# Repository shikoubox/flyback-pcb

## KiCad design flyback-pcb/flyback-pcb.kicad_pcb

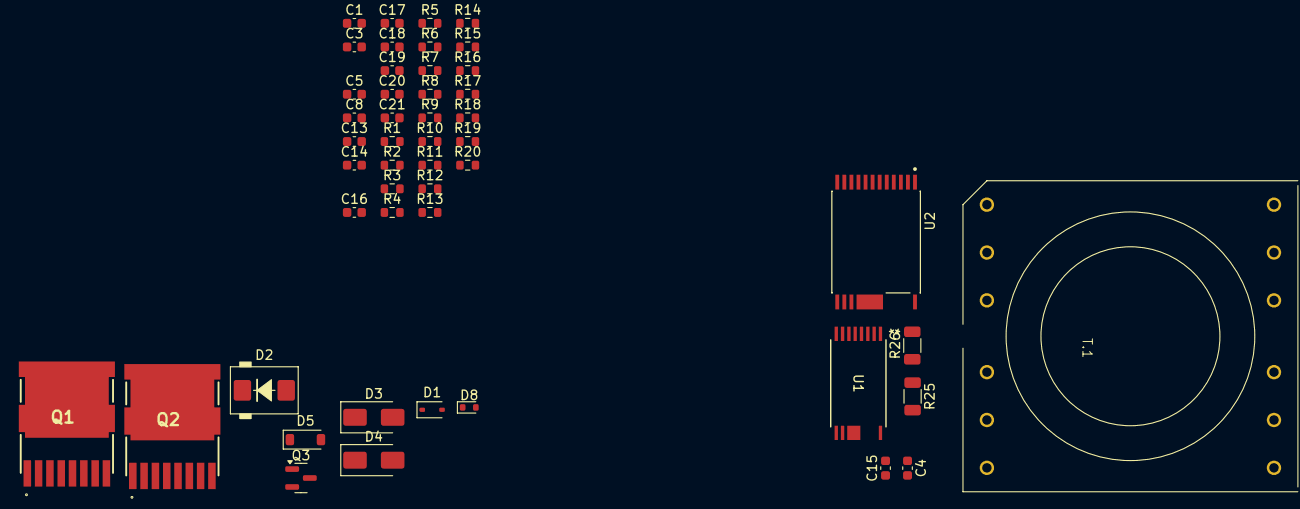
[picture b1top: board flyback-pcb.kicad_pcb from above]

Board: 2 copper layers, 48 parts (0 on the bottom side), 35 nets.

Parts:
C1: 470pF; C_0603_1608Metric
C3, C15, C16, C18, C19: 2.2nF; C_0603_1608Metric
C4: 39uF; C_0603_1608Metric
C5: 100uF; C_0603_1608Metric
C8: 1nF; C_0603_1608Metric
C13, C14: 330uF; C_0603_1608Metric
C17: 22uF; C_0603_1608Metric
C20, C21: 4.7uF; C_0603_1608Metric
D1: BAV19WS; D_SOD-323
D2: S3MB-13-F; D_SMBFL
D3, D4: S1G-E3/61T; D_SMA
D5: MMSZ5263; D_SOD-123
D8: BZT585-B10T; D_SOD-523
Q1, Q2: H-PSOF8L-11.68X9.80_1
Q3: MMBTA06; SOT-23
R1, R5, R7, R8: 20R; R_0603_1608Metric
R2: 2M; R_0603_1608Metric
R3, R4: 680K; R_0603_1608Metric
R6: 1.8M; R_0603_1608Metric
R9: 100R; R_0603_1608Metric
R10: 100K; R_0603_1608Metric
R11, R12: 47R; R_0603_1608Metric
R13: NCU18WF104F60RB; R_0603_1608Metric
R14: 0R; R_0603_1608Metric
R15: 3.65K; R_0603_1608Metric
R16: 11.8K; R_0603_1608Metric
R17, R18: 22R; R_0603_1608Metric
R19: 10R; R_0603_1608Metric
R20: 9mR; R_0603_1608Metric
R25: ERJ-8GEYJ395V; R_1206_3216Metric
R26: ERJ-8GEYJ105V; R_1206_3216Metric
T.1: B65879A
U1: MIN1072M-TL; MINSOP-16A_PWI
U2: INN3865CH801TL; IC_INN3865CH801TL

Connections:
GND: C13.2, C14.2, C16.1, C18.1, C19.1, C21.2, Q1.2 (S), Q1.3 (S), Q1.4 (S), Q1.5 (S), Q1.6 (S), Q1.7 (S), Q1.8 (S), R13.2 (-), R20.2, U2.2
HV_DC+: C1.2, C3.1, C4.1, C5.1, C15.2, R2.1, R3.1, R4.1, R25.2, T.1.1
HV_GND: C4.2, C15.1, C17.2, C20.2, D8.2 (A), T.1.4, U1.3 (SG), U1.6 (SG), U1.9 (GND), U1.10 (GND), U1.11 (S), U2.16_19
unnamed: C1.1, Q2.2 (S), Q2.3 (S), Q2.4 (S), Q2.5 (S), Q2.6 (S), Q2.7 (S), Q2.8 (S), R9.1
unnamed: C3.2, R7.2, R8.2
unnamed: C18.2, U2.5
unnamed: C19.2, U2.7
unnamed: C21.1, R19.2, U2.1
unnamed: D1.2 (A), Q1.9 (D), R1.1, R1.2, R5.1, R5.2, R12.1, T.1.7
unnamed: C8.1, D1.1 (K)
unnamed: D2.2 (A), R3.2, R4.2, T.1.3, U2.24
unnamed: D2.1 (K), R7.1, R8.1
unnamed: D3.2 (A), R9.2
unnamed: D3.1 (K), Q2.1 (G), U2.8
unnamed: D4.2 (A), T.1.5
unnamed: C17.1, D4.1 (K), Q3.3 (C), R10.2, R11.2
unnamed: C20.1, D5.2 (A), R15.1, U1.4 (BP), U2.14
unnamed: D5.1 (K), R11.1
unnamed: D8.1 (K), R16.1
unnamed: Q1.1 (G), U2.9
unnamed: C8.2, C13.1, C14.1, Q2.9 (D), T.1.6
unnamed: Q3.1 (B), R10.1, R16.2
unnamed: Q3.2 (E), R15.2
unnamed: R2.2, R6.1
unnamed: R12.2, U2.11
unnamed: R13.1 (+), R14.1
unnamed: R14.2, U2.6
unnamed: R17.2, U2.4
unnamed: R18.2, U2.3
unnamed: C5.2, R25.1, R26.1, U1.16 (D)
unnamed: U1.5 (L), U2.13
unnamed: R26.2, U1.1 (VBOT)
unnamed: R6.2, U1.8 (VTOP)
VBUS_GND: R19.1, R20.1
VBUS_IN: C16.2, U2.10

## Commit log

2024-10-01 Kicad initialize
2024-10-09 Day1_progress
2024-10-11 New symbol lib.
2024-10-18 Library and all symbols
2024-10-18 Cleanup
2024-10-20 Update flyback.kicad_sch
    found components
2024-10-22 Schematic
2024-10-22 INN3865
2024-10-22 component footprints
2024-10-22 Done_Schematic_v0.1
2024-10-22 inductor symbol and footprint
2024-10-22 Scematic_V.2.0
2024-10-22 Day2
2024-10-22 day2part2
2024-10-22 nearlyDone
2024-10-22 Minor changes
2024-10-22 Updated .gitignore and moved acdc to acdc sheet
2024-10-22 ul_tt10m symbol and component
2024-10-22 Descriptions
2024-10-22 nearNearDone
2024-10-22 fuseChange
2024-10-22 variable resistor
2024-10-22 USB+protection
2024-10-22 Re_design
2024-10-24 Re-done ac-dc
2024-10-24 Re-done USB
